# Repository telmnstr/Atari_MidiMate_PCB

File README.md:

# Atari_midimate_PCB
Atari "MidiMate" compat PCB in a direct-plug style like the FujiNet

- Based on sio2midi at https://ataribits.weebly.com/midi.html
- Different form factor for plugging straight into system with SIO on rear
- out/in cables pass through machines for linking MidiMaze

This is built for a one-time run of PCBs to do a 16 player MidiMaze setup at VCF using physical
midi cables. We will swap to FujiNet virtual midi network halfway through. 

Created in KiCad. I had to pull in the part for the DIN-5 from an extra library, which I included in this file.

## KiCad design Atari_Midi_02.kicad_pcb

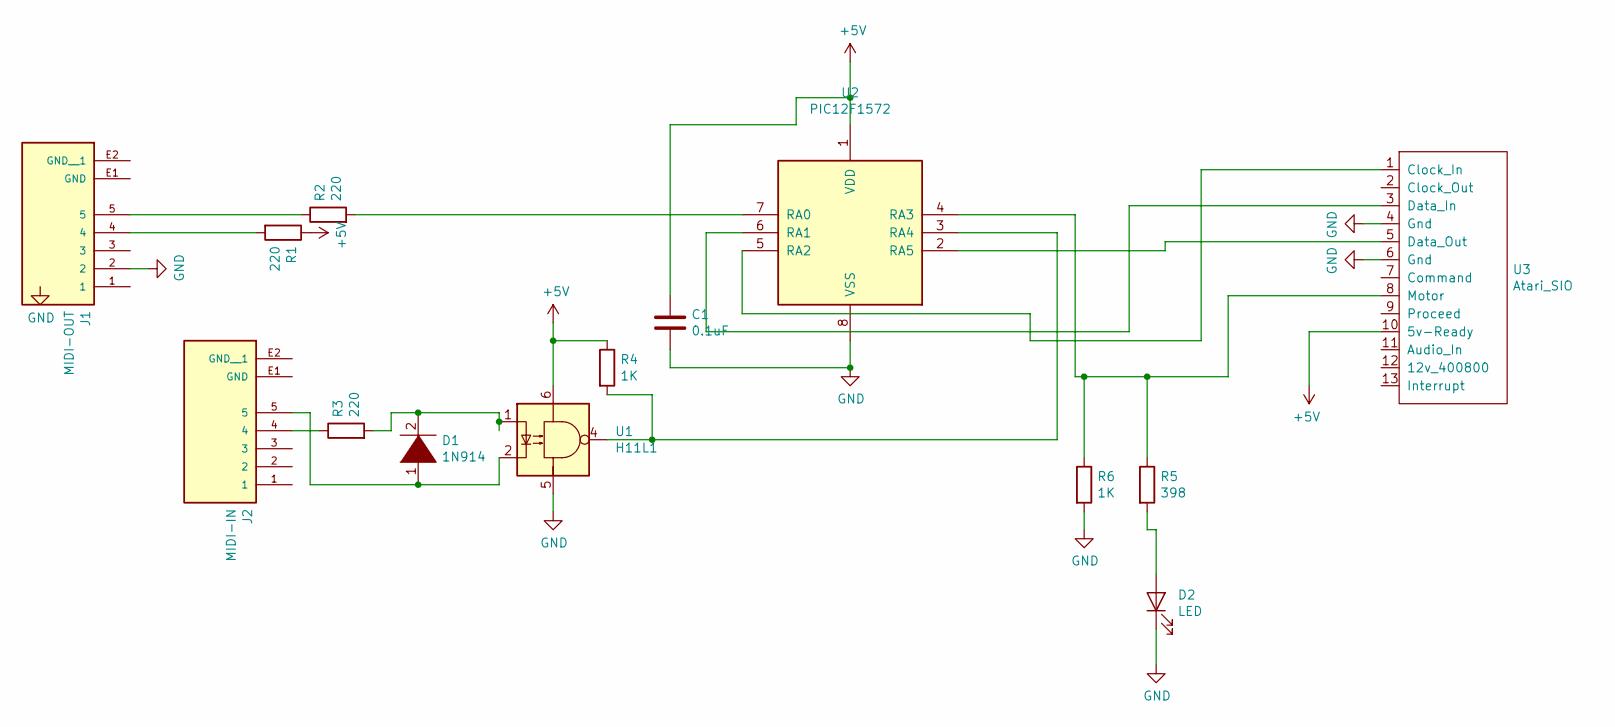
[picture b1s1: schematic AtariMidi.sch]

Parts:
C1: 0.1uF; C_Disc_D3.0mm_W1.6mm_P2.50mm
D1: 1N914; D_DO-34_SOD68_P7.62mm_Horizontal
D2: LED; LED_D3.0mm
J1: MIDI-OUT; CUI_SDS-50J; PARTREV 1.06/02-13-2020
J2: MIDI-IN; CUI_SDS-50J; PARTREV 1.06/02-13-2020
R1, R2, R3: 220; R_Axial_DIN0207_L6.3mm_D2.5mm_P7.62mm_Horizontal
R4, R6: 1K; R_Axial_DIN0207_L6.3mm_D2.5mm_P7.62mm_Horizontal
R5: 398; R_Axial_DIN0207_L6.3mm_D2.5mm_P7.62mm_Horizontal
U1: H11L1; DIP-6_W7.62mm
U2: PIC12F1572; DIP-8_W7.62mm
U3: Atari_SIO; AtariSIO

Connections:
+5V: C1.1, R1.1, R4.1, U1.6, U2.1 (VDD), U3.10 (5v-Ready)
GND: C1.2, D2.1 (K), J1.2, R6.2, U1.5, U2.8 (VSS), U3.4 (Gnd), U3.6 (Gnd)
unnamed: D1.1 (K), J2.5, U1.2
unnamed: D1.2 (A), R3.2, U1.1
unnamed: D2.2 (A), R5.2
unnamed: J1.4, R1.2
unnamed: J1.5, R2.1
unnamed: J2.4, R3.1
unnamed: R2.2, U2.7 (RA0)
unnamed: R4.2, U1.4, U2.3 (RA4)
unnamed: R5.1, R6.1, U2.4 (RA3), U3.8 (Motor)
unnamed: U2.2 (RA5), U3.5 (Data_Out)
unnamed: U2.5 (RA2), U3.1 (Clock_In)
unnamed: U2.6 (RA1), U3.3 (Data_In)

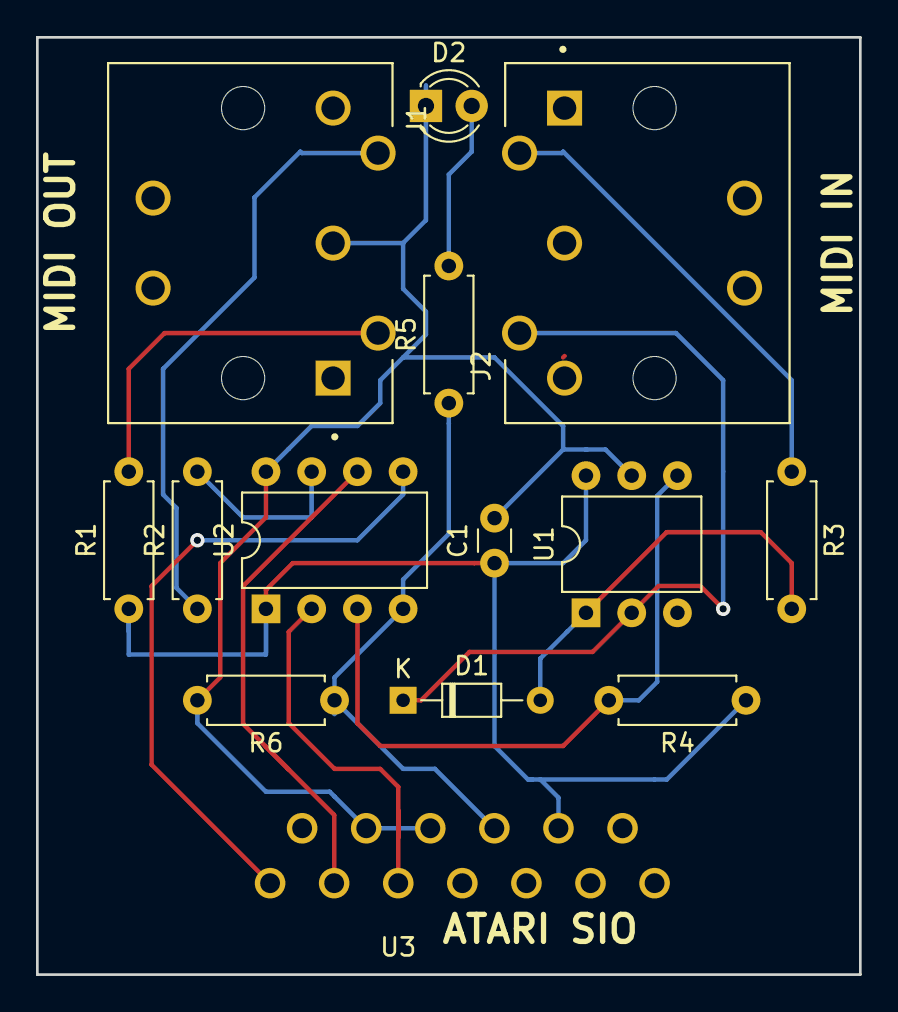
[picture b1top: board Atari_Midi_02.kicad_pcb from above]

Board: 2 copper layers, 45.7 x 52.1 mm, 14 parts (0 on the bottom side), 14 nets.

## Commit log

2022-02-18 Initial batch of files
2022-02-18 Adding libraries that are needed, the 5-pin DIN (SDS-50J) and Atari SIO
2022-02-21 Added two images (Screengrabbed from KiCad) so Reggie can proof it for me.
